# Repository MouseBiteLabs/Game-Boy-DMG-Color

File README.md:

# Game Boy DMG Color

This is my design for an original Game Boy (model name DMG) with native Game Boy Color support, and a handful of improved features! This is an original creation - newly designed PCBs, with only some necessary components harvested from an original Game Boy and Game Boy Color (no hardware emulation – this project uses the original CPU). Here are the project goals:
-	An original Game Boy aesthetic, using the original Game Boy shell and interface (link port, volume wheel, power switch, etc.), but with the capability of playing both Game Boy and Game Boy Color games.
-	A nice, large IPS screen – the GBC Q5 XL IPS Backlight with OSD kit – with brightness and color palette control via the "navigation switch" housed where the contrast wheel used to be. (I will refer to the PCB attached to the Q5 screen as the “Q5 board”)
-	A modernized, efficient switch mode power supply that can run off 4x AA batteries or input from the DC jack, just like the original DMG. Testing shows that playing with NiMH AA batteries can yield more than 18 hours of gameplay at normal settings (AKA, the way I normally play it - maximum brightness and headphones). 
-	Louder, warmer sound through a modern audio amplifier.
-	The option for tactile switches for the face buttons - like the GBA SP.
-	The option for backlit buttons, with multiple color modes and brightness control.
-	No externally viewable case modifications, outside of trimming the DMG power switch cover for Game Boy Color game compatibility.

The code name for this project is DMGC. This console uses four PCBs, just as the original DMG model did - a CPU board (DMGC-CPU), display board (DMGC-IPS), power board (DMGC-PWR), and headphone board (DMGC-HDP). All circuit board assemblies have their own separate folders in this repository which contain detailed descriptions of operation, source files for schematics and board layouts (designed using Eagle), exported Gerber files, and some other relevant files. 

**Do you want to make one?** Then you NEED TO READ this entire page. Seriously. All your questions will be answered.

## Disclaimer

**Before I go any further, please read this VERY important disclaimer, if you are thinking about making this yourself. Don't let this picture happen to you!**

I made this project first and foremost **for my own purposes**. Nearly all of the features I have included are things I **personally** wanted. I have tried my hardest to make the project modular, if others would like to improve or change things easily, and I have also tried very hard to make the design somewhat less prone to potential errors during assembly (such as spacing out power pins on the FFC connectors). But in the end, every decision I made was for what I wanted the final product to be, with my skill level in mind.

Schematics, gerbers, and the BOM are provided in the various folders. If you choose to build this project yourself, be warned - this is a considerably advanced, and expensive build. You must be comfortable with the fact that you may lose or damage expensive components. **You are 100% liable for any damage done to your property or yourself. I am not responsible for any damage or loss of property incurred while attempting this project, or after completion of the project - you alone accept all risk.** While I am confident in this design, I cannot claim full compatibility with every system configuration. And there may be latent issues that have yet to crop up. I will update this repo if I encounter any, and if you see anything I may have missed, or some dubious design choice, feel free to ask questions or comment as such. Corrections are welcome. However, I **will not** obligate myself to providing tech support. You accept all risks and costs associated to this build if you choose to attempt it.

**DO NOT attempt this project if you are uncomfortable or inexperienced with detailed electronics troubleshooting, or are not proficient in soldering! You will AT MINIMUM need to be proficient in drag soldering and hot air reflowing. If you have not gained proficiency in these soldering skills, DO NOT ATTEMPT THIS PROJECT.**

If you attempt the build, start with trying to assemble DMGC-PWR-01. This is the toughest board to assemble, and it requires no donor components.

## Bill of Materials (BOM)

There are a handful of categories for the parts you need for this build. Please review all of them! The total BOM cost will come out to anywhere between $200 and $250 (NOT including the cost of a donor Game Boy Color console!) depending on the options you choose, which OEM parts you re-use, and any potential deals you can get on certain parts. Note that with the exception of a few components from a donor Game Boy Color, *most* of the electronic parts are brand new.

### I. Circuit Boards

First and foremost, the circuit boards. I have created these four boards myself, and you will need all of them:

1) <a href="https://mousebitelabs.etsy.com/listing/1317688422/game-boy-dmgc-cpu-board?utm_source=Copy&utm_medium=ListingManager&utm_campaign=Share&utm_term=so.lmsm&share_time=1694126428997">DMGC-CPU-01</a>: The CPU board, where the brains are held
2) <a href="https://mousebitelabs.etsy.com/listing/1331663235/game-boy-dmgc-ips-board?utm_source=Copy&utm_medium=ListingManager&utm_campaign=Share&utm_term=so.lmsm&share_time=1694126445880">DMGC-IPS-01</a>: The front display board
3) <a href="https://mousebitelabs.etsy.com/listing/1317694018/game-boy-dmgc-pwr-board?utm_source=Copy&utm_medium=ListingManager&utm_campaign=Share&utm_term=so.lmsm&share_time=1694126458438">DMGC-PWR-01</a>: The power supply board
4) <a href="https://mousebitelabs.etsy.com/listing/1331671237/game-boy-dmgc-hdp-board-headphone-board?utm_source=Copy&utm_medium=ListingManager&utm_campaign=Share&utm_term=so.lmsm&share_time=1694126482746">DMGC-HDP-01</a>: The board that holds the headphone jack

I have provided the zipped Gerbers and ordering details in each of the board folders above, <a href="https://www.pcbway.com/project/member/?bmbno=BC9D73E0-EF3D-4F">as well as shared projects on PCBWay.</a> For full disclosure, if you buy the PCBs from PCBWay, I will receive 10% of the total sale towards buying more boards from PCBWay. You can alternatively use these Gerbers at other PCB fabricators if you would like. 

### Purchase from My Website

You can purchase this circuit board at my website, [https://mousebitelabs.store](https://mousebitelabs.store). Click the following image to be directed to the specific item listing:

### Purchase from Etsy

I also offer the board on Etsy, if you would rather purchase through there - click the banner to be redirected.

### Purchase from insideGadgets

And finally, <a href="https://shop.insidegadgets.com/product/game-boy-dmg-color/">insideGadgets sells these boards partially assembled!</a>

### II. Brand New Electronic Parts

The DMGC uses mostly all-new parts. This isn't a direct-transfer style project! The master BOM with every electronic component required for the four circuit boards are provided in this root folder in Excel format. Furthermore, each folder for each board will contain their section of the BOM near the bottom of each README that contain all of the electronic components needed for that specific circuit board. Note that some parts may be out of stock at the links provided, but many can be found at alternate other retailers online, or have a proper substitute. <a href="https://www.mouser.com/ProjectManager/ProjectDetail.aspx?AccessID=6600c1bb14">Here is a saved cart from Mouser that contains all the parts in the BOM Excel, including some duplicates.</a> Double check to see if any parts are missing, and consider ordering multiples of some parts. There also may be some parts you want to remove (like the tactile switches).

**If a part is backordered, or out of stock** - check the Excel file, or the BOMs listed at the bottom of each board's folder in this repo. There may be alternate part options. You can also check for stock at places like Digikey. And you can always use Octopart.com to help find in-stock parts at other websites. I can't maintain the cart for every out-of-stock part, so please do some research :)

### III. Game Boy Electronic Parts

*This project requires at the very least a donor DMG console and a donor GBC console.*

There are a handful of parts that I have not located aftermarket substitutes for, and will therefore necessitate an original Game Boy console to salvage from. Please note that removing these parts is not a trivial task, and **requires advanced soldering and desoldering skills to be successful.**

The following parts are required from an original Game Boy Color console:

  -	U1 – CGB CPU (all revisions *except* REV E, which is *incompatible*)
  - X1 – 8.388 MHz crystal oscillator

The following parts can be salvaged from a Game Boy Color, but aftermarket options exist:

  - U2 – LH52256CVTXIZ (SRAM); alternate: https://mou.sr/3f8G0Mi
  - EM10 – input filter; alternate: https://mou.sr/3FiMvXw

The following parts are required from an original Game Boy (DMG) console:
  
  -	SW1 - Power switch
  -	DC jack
  -	Headphone jack

The following part is required from an original Game Boy (DMG), or a Game Boy Four Player Adapter:

  -	EXT port

The following parts can be salvaged from an original Game Boy (DMG), but aftermarket options exist:

  -	VR1 – Volume dial
  -	P1 – Cartridge connector

### IV. External Build Parts

The following is the high-level BOM - basically, the Game Boy part. Note that parts that deviate from the ones listed here (like different shell designs) might necessitate different fitment modifications, or end up being incompatible. Note that this list is not a comprehensive list of all the places you can get these parts. I encourage you to search around if you can't find what you want here.

-	**Shell:** I generally recommend the Funnyplaying "IPS Ready" ones if you don't want to trim anything, but the color and style options are limited. If you don't use these, then you're on your own for how to prepare it - generally, you can follow guides for preparing a Pocket for an IPS screen kit.
    - RGRS:	<a href="https://retrogamerepairshop.com/collections/game-boy-dmg-shells/products/game-boy-dmg-original-new-shells-factory-a?variant=32530346967114">Game Boy DMG Shell – Factory A</a> [Note: this one requires trimming!]
    - Funnyplaying: <a href="https://funnyplaying.com/products/dmg-ips-coustom-housing">DMG IPS Q5 Custom Housing</a>
- **Screen Kit:** This is the important one. You need this specific type of kit - the Q5 IPS with OSD. It goes by many names, the maker is Hispeedido (*not* FunnyPlaying). Kits that have the screen laminated to a GBC lens are *not* compatible, but kits that include a lit-up logo on the bottom part of the screen are fine to use. Make sure you DO NOT get any Game Boy DMG versions - they are not compatible! Also, be sure to test this screen kit before installing it, preferrably with an original Game Boy Color. Sometimes they arrive damaged, and once you've installed, it may not be possible to get a refund.
  - RGRS: <a href="https://retrogamerepairshop.com/products/game-boy-color-q5-ips-backlight-with-osd?variant=37646279213228">GBC Q5 XL IPS Backlight with OSD</a> OR <a href="https://retrogamerepairshop.com/collections/gbc-displays/products/game-boy-color-q5-osd-ips-kit-with-color-changing-logo?variant=41819042185388">Game Boy Color Q5 OSD IPS Kit with Color Changing Logo 
  - AliExpress: <a href="https://www.aliexpress.us/item/3256801650459088.html?spm=a2g0o.productlist.main.1.758e53f17WUFK2&algo_pvid=24ef67e3-d608-4269-a663-05eafed1bd17&algo_exp_id=24ef67e3-d608-4269-a663-05eafed1bd17-0&pdp_npi=3%40dis%21USD%2145.9%2145.9%21%21%21%21%21%4021224e9b16816641208271256d074d%2112000017802039303%21sea%21US%210&curPageLogUid=dCymHIE0cr4X">GBC Q5 IPS LCD Kit</a>
  - HHL: <a href="https://handheldlegend.com/products/game-boy-color-ips-lcd-q5-hispeedido">Game Boy Color IPS LCD Q5 - Hispeedido</a>  
- **Screen Centering Bracket:** You can find the design file for this bracket in the DMGC-IPS-01 folder. It's a custom designed bracket I made that *is required* for holding the screen in place. You will need access to a 3D printer for this part, or you can order it online from 3D printing services by uploading the file.
  - <a href="https://github.com/MouseBiteLabs/Game-Boy-DMG-Color/blob/main/DMGC-IPS-01/dmgc_q5_bracket.stl">DMGC Q5 Bracket 3D Model .stl File</a>
-	**Lens:** You must get the "IPS" style of lens, as the viewing area is larger.
    -	RGRS: <a href="https://retrogamerepairshop.com/collections/dmg-lenses/products/funnyplaying-dmg-q5-ips-lens?variant=39626455187628">FunnyPlaying DMG Q5 IPS Lens</a>
    - FunnyPlaying: <a href="https://funnyplaying.com/products/dmg-retro-pixel-ips-glass-lens">DMG RetroPixel IPS Glass Lens</a>
- **Buttons:** Funnyplaying models are generally OEM-like (IMO), but you can also use OEM ones. For the above build, I used Kitsch-Bent silicone buttons. Bonus: NES controller buttons fit inside the DMG.
  -	Kitsch-Bent: <a href="https://store.kitsch-bent.com/products/silicone-buttons?variant=40627510771907">Clear Silicone DMG Buttons</a>
  - RGRS: <a href="https://retrogamerepairshop.com/collections/dmg-buttons">DMG Buttons</a>
  - LabFifteen: <a href="https://labfifteenco.com/en-us/collections/game-boy-dmg-buttons">Game Boy DMG Buttons</a>
  - FunnyPlaying: <a href="https://funnyplaying.com/products/gb-dmg-custom-buttons">DMG Custom Buttons</a>  
- **Membranes:** Important, but very forgettable! You will need them even if you install tactile switches. You will, however, *not* need them if you use the Kitsch-Bent buttons.
  - RGRS: <a href="https://retrogamerepairshop.com/collections/dmg-buttons/products/funnyplaying-game-boy-dmg-silicone-button-contact-pad-membranes">FunnyPlaying Game Boy DMG Silicone Button Contact Pad Membranes
  - FunnyPlaying: <a href="https://funnyplaying.com/products/replacement-silicone-pads-for-gb-dmg">DMG Replacement Silicone Pads</a>  
- **Speaker:** There are tons of options for this as well, including using the OEM one.
  - RGRS: <a href="https://retrogamerepairshop.com/collections/dmg-audio/products/funnyplaying-clear-game-boy-dmg-original-speaker?variant=37728957726892">FunnyPlaying Clear Game Boy DMG Original Speaker</a>
  - FunnyPlaying: <a href="https://funnyplaying.com/products/clear-dmg-speaker">Clear DMG Speaker</a>
- **Battery Tabs:** This one is another part I commonly forget about. You can use a salvaged set of tabs, or order new ones.
  - RGRS: <a href="https://retrogamerepairshop.com/collections/dmg-power/products/game-boy-dmg-original-high-quality-replacement-battery-contact-terminals?variant=37893135794348">Game Boy DMG Original High Quality Replacement Battery Contact Terminals
- **Stickers:** Completely optional, but they can really bring a build together. Especially if you have custom DMG Color stickers!
  - Nextstopplease: <a href="https://nextstopplease.square.site/product/dmgc-label/230?cp=true&sa=true&sbp=false&q=false">DMGC Labels</a>

<b>Buying from RGRS? Consider helping out some cool people with these referral links:</b>
- <a href="https://retrogamerepairshop.com/?ref=ltyD2rUX">CodyWick</a>
- <a href="https://retrogamerepairshop.com/?ref=HSj4v5OO">JackV</a>

<b>Or use one of these discount codes at checkout:</b>
- Nataliethenerd
- B23N
- Tito

Note that the IPS kit I have listed is the *easiest* IPS kit to use that is compatible with this build. It includes an image centering feature, so you don't need to fiddle with centering it manually in the shell. Other kits likely would not center nicely in the DMG shell! <a href="https://retrogamerepairshop.com/collections/gbc-displays/products/game-boy-color-2-6-ips-high-brightness-drop-in-backlight-lcd-kit?variant=41398632251564">This kit works electrically, but requires you to center the image yourself.</a> If you end up making some sort of 3D-printed bracket to support this screen, feel free to share it here.

## Assembly

You can check out Tito's video on the DMGC to get an idea of how the assembly process generally goes.

Here are some pictures of the assembly process *after* testing the functionality of all the boards separately. Detailed images of the circuit boards alone are shown in their respective folders. These pictures are of a previous revision, v1.2, but the process remains the same. You may notice some minor cosmetic differences in these pictures from the current revision boards.

**I highly recommend reading the information in the Troubleshooting and Testing folder above. In it, I detail the testing procedure that I follow before fully assembling a DMGC. It is far easier to do this than to have to disassemble things when something doesn't work.**

First, I started with the back half of the DMG shell. The PWR board needs five ~2.25" wires that wrap around the screw post on the side of the shell. In addition to the PWR board connections, the HDP board needs four ~2.6" wires. Also, the flat flex cable (FFC) should be inserted into the CPU board first, because the connector will be inaccessible after screwing the CPU board in the shell. After I soldered all the wires between the three boards and secured the FFC, I placed the assembly in the shell, and secured it with the proper screws. I put a game in the cartridge slot to keep the CPU board in place easier while assembling.

Before placing the power switch cover in, I cut a notch in it so that it wouldn't prevent Game Boy Color games from being played in the system. In the left picture below I’m using Game Boy games, and in the right picture I'm using Game Boy Color. And you can see that the power switch is blocked from turning on by the GBC cartridge for the original model.

After the back half was done, I prepared the Q5 board solder pads. I cut six 30 gauge wire segments and soldered them on the brightness, palette, battery, and OSD input pads. These will be soldered to the rear of the IPS board after installed. You don't need to include a wire to the GND pad.

For the top half of the shell, as per instructions on a similar DMG IPS kit that uses the Q5 screen, I very carefully cut ~1 mm of plastic around the border of the viewing port, and trimmed any extra plastic to make the surface underneath the lens smooth (there are "IPS ready" shells that should not require this cut). I used a black paint marker to color in the edges of the newly cut plastic, so they would not be visible at an angle. And I trimmed two posts off of the shell so the screen would fit flush against it. 

Then I installed the front lens, and placed the screen, backed with the 3D printed bracket, into the front half of the shell. I made sure to clean up any stray fingerprints or dust while assembling this part. Once the bracket was placed and flush with the shell, I put the buttons in and placed the IPS board over top, slid the Q5 screen FFC into the connector on the PCB (making sure it fit without any added stress on any connections), and secured it all in place. Then I *very carefully* soldered the wires from the Q5 board onto the appropriate pads on the IPS board - making sure not to melt any plastic on the shell.

**Note: Be extremely careful with the screen. It is fragile. If you break it, you can sometimes buy one separately.

If you installed the 7-pin headers for programming the ATTINY easier, you might want to tape off the headers with kapton tape. If everything is installed correctly, these shouldn't interfere with anything on the CPU board after the halves are screwed together (C47 is the closest component), but you may want to consider it anyway.

After that, it was just a matter of connecting the FFC from the CPU to the IPS board, tucking it under the boards ensuring no kinks or sharp bends, and screwing it together. Once assembled, I opened the OSD menu for the IPS kit (Select + A + B) and changed the vertical and horizontal offsets (my values were 78 and 29, respectively) to center the image on the screen. The image centering function is one of the biggest reasons I chose this IPS kit.

I suggest running the color tests in the <a href="https://github.com/pinobatch/240p-test-mini/releases/">240p test suite ROM</a>, if you have a flash cart to run it on. It will tell you if you have any poor connections on the FFC lines - the screen might work, but you might be missing a connection on one of the 15 RGB pins! If your colors look off, reflow the connections on the top row of pins on the CPU and/or the FFC connectors (the issue may be on the CPU board, *or* the IPS board). This picture (provided by <a href="https://retrogamerepairshop.com/?ref=HSj4v5OO">JackV</a>) shows a before and after pic for reflowing a few mis-soldered color pins.

Next to an original DMG… one can really see the improvements!

## Auxilliary Controls
### Q5 XL IPS Backlight with OSD
-	Select + A + B: Open the OSD menu
-	Select + A: Enter
-	Select + B: Exit
-	A: Increase
-	B: Decrease

### Navigation Switch
-	Rock up: Advance screen brightness setting
-	Rock up/Hold: Toggle on-screen battery indicator
-	Rock down: Advance screen color pallete setting
-	Rock down/Hold: Toggle on-screen pixel grid
-	Push in: Toggle button LED color setting
-	Push in/Hold + D-pad Left: Decrease button LED brightness
-	Push in/Hold + D-Pad Right: Increase button LED brightness
-	Push in/Hold when turning on power switch: Disable LEDs until another power cycle

## Power Draw Measurements
For these estimates, battery life is calculated using four eneloop pro NiMH AA batteries (total of ~11800 mWh). Keep in mind that these are very rough estimates. I tried to be conservative in the power draw measurements, so hopefully these numbers represent a *mostly* worst case. Actual playtime *will* vary due to a variety of factors - changes in efficiency and performance as the battery voltage changes, differences in game audio, etc.

I measured the power draws using a MiniWare MDP-XP Mini Digital Power Supply, and estimated the average power draw shown on the display (I tried to bias towards a higher value). Input voltage was set to 4.4 V, just above the point where the power LED dims. I tested with the Legend of Zelda: Link's Awakening, letting the game sit on the title screen after the intro cinematic, where sound is relatively loud and the screen is mostly white. The audio gain on the test console is set to ~0.38 (see CPU board for more detail on this gain value - a higher gain can greatly impact power draw at high volumes out of the speaker).

| Test Criteria | Power Draw | Estimated Battery Life |
| ------------- | ------------- | ------------- |
| IPS max brightness, NeoPixel LEDs max brightness (white), speaker volume 100%, Everdrive X5	| 1150 mW	| 10.3 hr |
| IPS max brightness, NeoPixel LEDs off, speaker volume 100%, Everdrive X5 | 900 mW	| 13.1 hr |
| IPS max brightness, NeoPixel LEDs off, speaker volume 100%, original cartridge | 750 mW | 15.7 hr |
| IPS max brightness, NeoPixel LEDs off, headphones, Everdrive X5	| 725 mW	| 16.3 hr |
| IPS max brightness, NeoPixel LEDs off, headphones, original cartridge | 650 mW	| 18.2 hr |
| IPS min brightness, NeoPixel LEDs off, headphones, original cartridge	| 475 mW	| 24.8 hr |

*Note: If powering through the DC jack instead of batteries, an OEM adapter may not be able to supply enough power to the DMGC at maximum settings. Furthermore, <a href = "https://retrogamerepairshop.com/products/dmg-game-boy-original-dmg-usb-power-cord-adapter?variant=39454726455468">cables like these</a> will require at least ~200 mA output from the USB port for reliable operation at all settings. (USB 1.0 and 2.0 are likely not sufficient for higher loads, such as with the button LEDs on)*

## Audio Recordings and Spectrum
I mentioned the sound of the DMGC is "warmer" than an original GBC - it's bassier with less buzzing background noise (owing mostly to the modernized power supply). I connected the headphone jack to my computer's microphone input, and used Audacity to obtain line out recordings. Then I graphed the spectrum using Audacity's "plot spectrum" analysis tool. You can see the larger gain at the lower frequencies in the spectrum plot of the DMGC. I also took some recordings of the pro-sound output as well - it's even cleaner than from the amplifier. I'm not an audiophile, but I'm pretty sure the DMGC all-around sounds nicer, at least through headphones. Listen for yourself! (GitHub only allows for video files to be embedded, MP3 files are provided above)

### Original GBC Audio

https://user-images.githubusercontent.com/97127539/180215249-4b21aca1-a9fd-430a-a870-95bf4837e4da.mp4

### DMGC Audio

https://user-images.githubusercontent.com/97127539/180215280-5e533449-5116-4848-a94b-92f8979db334.mp4

### DMGC Audio (Pro-sound)

https://user-images.githubusercontent.com/97127539/197674317-792a8da5-ebd5-4ef6-9e8d-8eab0cbf9284.mp4

### Original GBC Audio Spectrum

### DMGC Audio Spectrum

### DMGC Audio (Pro-sound) Spectrum

## Possible Additions/Changes
Want to improve this project? Maybe try one of these things (because I probably won’t):
- This console uses 4x AAs instead of a single rechargeable battery in order to maintain the feel and weight of the original DMG model, but an obvious change to the build is to utilize a LiPo battery with proper battery management. The DC jack could be repurposed to charge the battery instead. With the advent of affordable rechargeable AAs, the appeal of the AC adapter is diminished, so this would be a good repurposing. However, the maximum output current of most DMG AC adapters is rated for ~200mA at ~6V, so charging would be considerably slower than, say, fast USB-C charging.
- Restoring the IR functionality of the GBC could also be done, as there is ample space for it on the circuit board and shell - I just do not trust myself with forming plastic to look nice, and it wasn't at all an important part of the build for me.
- Finding aftermarket equivalents for all the different required DMG parts would be ideal, instead of using a (hopefully broken) DMG for a donor console. For my personal build, I used original DMG components because I had a damaged console lying around, but you can easily find DMG-style volume wheels and cartridge connectors online. The tricky parts are as follows:
  - A GBC EXT port can be used in place of the DMG one (but would look kind of weird in the DMG EXT hole in the shell).
  - There are a few power switches I've ordered to try out in place of the DMG one, but I haven't gotten around to testing them yet. There's no one fully drop-in replacement that I've found, though, so it would require circuit modifications.
  - I haven't been able to locate a headphone jack exactly the same as the DMG one, but the circuit could be adapted to accept a different style.
  - The DC jack could be tricky. I haven't looked very hard for any kind of replacement for this.
- Any other of the various popular GBC mods could be incorporated if desired - bluetooth, overclocking, etc. With the ATTINY on the IPS board, one could incorporate button combinations to interface with these mods without the need of any additional buttons or (*shudder*) touch controls.
- I thought about adding LEDs to the *back* of the front PCB, so that light would emit out the edges of the console with a translucent or transparent shell, but I never got around to trying it out.

## Potential Issues/Annoyances
-	When the button LEDs are on max brightness, using the NeoPixel LEDs specifically (especially on the white color setting), a ~1 kHz whine can be heard through the speakers or headphones. I attempted to remove this whine with different methods – adding filtering to the supplies, using separate supplies for the audio/LEDs, etc. –  this lowered the noise amplitude, but I wasn’t able to remove it completely. And obviously adding a filter on the audio output is a no-go since 1 kHz is smack dab in the middle of the audible range. Changing to different color settings can reduce the volume of the whine, red in particular seems to be quite low, and setting the LEDs at lower brightness levels (or just completely off) removes it. So just don’t play with the LEDs on really bright if it bugs you! I kept the color sweep during power-on enabled on every color setting - if you want to disable the LEDs for the entire play session, hold the navigation dial in when you turn it on (but at that point... why did you bother adding the LEDs in the first place?)
-	The original DMG A/C adapter that plugs into the DC jack cannot support play with maximum settings (backlit buttons, maximum brightness, maximum speaker volume, flash cart). If you start up the Game Boy with less than maximum settings, then during gameplay increase the load on the power supply such as by increasing the screen brightness or maxing out the volume on the speakers, the console may shut off. If you're powering the console through the DC jack, I suggest using a USB adapter cable into a USB 3.0 port (or some style of USB wall charger)

## Frequently Asked Questions

I'll update this section as more people begin to build these.

**Q: How do I lower the brightness of the power LED? I can't see anymore.**

A: You can pick a different LED model with lower brightness, or you can simply increase the resistance of R1 on the IPS board. Higher resistance = lower brightness. I would try 10 kΩ first if 5.6 kΩ is too bright. (If you want to dim the low power level LED brightness, increase R2 resistance as well!)

**Q: My EM10 has an extra leg in-between two of the other ones. Can I use this part?**

A: Yes, just bend up the extra pin so that it doesn't contact any of the nearby pads. It is an unused anchor pin.

**Q: Why does the audio sound like [not normal]? (Usually asked while testing during the middle of a build)**

A: The audio will sound terrible if you do not have your IPS kit connected. You can use the CPU board's FFC connnector for the IPS kit if you would like to test it without the IPS board in the middle. Furthermore, the speaker will be muted if you do not install the headphone board.

**Q: Sometimes the power switch is finnicky and the system won't power on consistently. Sometimes the IPS screen will turn on, but only the backlight, not the actual image. What gives?**

A: Clean your power switch (without batteries inserted or power applied) by dripping isopropyl alcohol inside and flipping it off and on a few times. This will hopefully clear up debris or oxidation. Opening up a DMG power switch isn't the funnest thing to do. I have found that if the IPS kits receive intermittent power while turning on, it will lock out their image processing until you power cycle. It's not damaging, just annoying.

**Q: When I have the front and back halves of the DMGC separate, everything powers on correctly. But when I screw the two halves together, it doesn't turn on. Why?**

A: Check to make sure the wires connecting the CPU and PWR boards do not have long stubs of wire sticking up out of the CPU board. The IPS board's navigation dial has metal housing that can short these wire stubs together if they are too long. Trim them short so they don't touch the metal shielding.

**Q: Sometimes when I'm using batteries and turn the power switch on, nothing happens.**

-AND/OR-

**Q: Sometimes when I play my DMGC, and I set it on the table too hard, the game resets. Why?**

A: Usually this is because you're using NiMH AA batteries, like eneloop pros. These batteries have *slightly* shallower positive tabs than regular alkaline AA batteries. This makes contact from the batteries to the tabs not as robust as regular AA batteries. Unfortunately this is a problem on *ALL* DMG consoles, not specifically the DMGC. This could be due to a poor connection on any one of the four batteries inside the bay. You can swap out battery contacts that stick out a bit farther that make better contact with the batteries, or you can try reseating or literally spinning the batteries in the battery bay to make better contact. (Or, you could always use regular AA batteries or an A/C adapter!)

**Q: Can I use this with a DMG CPU?**

A: No, this is only for use with Game Boy Color CPUs. There are some other projects around that recreate the DMG, <a href="https://github.com/kamicane/DMG-01-B">like this one</a>.

**Q: I really like this project, but I just wish it was in a smaller, more cramped shell, with way worse battery life. Can you help?**

A: <a href="https://imgur.com/a/JgXPnYc">I'm working on it.</a>

## Acknowledgements
-	The board outlines and many of the footprints for the DMG components from <a href="https://gbdev.gg8.se/files/schematics/">this DMG recreation project</a> were used for reference on the original revision of the project, so very special thanks to Rolf, bit9, and nitro2k01!
-	Thank you to gekkio for their <a href="https://gbhwdb.gekkio.fi/">Game Boy repository</a> and <a href="https://github.com/Gekkio/gb-schematics">github</a>: I referenced many of the DMG and GBC resources during this build, even just for looking at pictures of different PCBs.
-	Immense thanks to the users of the r/Gameboy and gbdev discord servers for technical resources, troubleshooting/feedback, and suggestions. Could not have done this without your support. Shout out to kevtris for design feedback and lidnariq for troubleshooting support!
- Thank you to Tito, aka Macho Nacho, for <a href="https://www.youtube.com/watch?v=4U8Tqu7uxLo&ab_channel=MachoNachoProductions">his amazing video covering the project.</a>
-	Of course, huge thank you to everyone who has <a href="https://ko-fi.com/bucketmouse">donated and supported me</a>, and to those who have built their own DMGC! I love seeing pictures of builds, so feel free to share them with me on Twitter, <a href="https://discord.gg/Y5aDvCcpbX">discord</a>, or via email!

## License
<br />This work is licensed under a <a rel="license" href="http://creativecommons.org/licenses/by-sa/4.0/">Creative Commons Attribution-ShareAlike 4.0 International License</a>. You are able to copy and redistribute the material in any medium or format, as well as remix, transform, or build upon the material for any purpose (even commercial) - but you **must** give appropriate credit, provide a link to the license, and indicate if any changes were made.

This project is the culmination of nearly a full year of research, development, and testing. I have made this project completely open-source, and have put hundreds, if not *thousands* of hours of work into it, so that many people can enjoy it. **Please** give me appropriate credit where credit is due.

©MouseBiteLabs 2022

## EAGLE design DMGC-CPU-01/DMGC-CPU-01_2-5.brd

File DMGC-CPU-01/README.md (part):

# DMGC-CPU-01

*The image above of the assembled board is of v2.0, not the current revision of v2.4. The differences in appearance are minor, see below.*

The CPU board houses the majority of the electronics in the DMGC. Parts harvested from the original GBC include the CPU, SRAM, and crystal oscillator. EM10 may be transferred as well, but a good enough replacement is included in the BOM if you need a new part. The power supply modifications, the new audio circuit, and a handful of omissions like the IR communication and some of the now-unnecessary LCD pins differentiate this build from the original GBC. But many connections and component values are pulled from the official GBC schematic (linked below).

For a technical explanation of the CPU board, please view the README in the Technical folder.

## Board Characteristics
The zipped folder contains all the gerber files for this board. 

-	Layers: 2
-	Thickness: 1.2 mm
-	Surface Finish: ENIG or HASL
-   **NOTE: For v2.4, when ordering PCBs, add this note to the order: "The file milling.gbr contains outlines for plated slots. Please add plated slots on the PCB according to this layer." V2.5 does not require this note.**

*HASL will work, but will potentially be more difficult for soldering fine-pitch parts like the CPU and FFC connector.*

<a href="https://www.etsy.com/listing/1317688422/game-boy-dmgc-cpu-board">**I sell this board on Etsy, so you don't have to buy multiples from board fabricators.**</a>

You can alternatively use the zipped folder at any board fabricator you like. You may also buy the board from PCBWay using this link (disclosure: I receive 10% of the  sale value to go towards future PCB orders):

## Customization Options

This section will explain all of the different customization options available on this board while assembling.

### Adjusting Volume Range

You can adjust the maximum volume coming out of the speakers and headphones by modifying R30 and R32 values. Increase R30 and R32 to decrease the maximum volume; decrease R30 and R32 to increase the maximum volume. Choose the same values for both of these resistors, otherwise you'll have lopsided audio channels. After some trial and error, here's my approximations of some different values of resistors:
- Choosing 100 kΩ for a gain of ~0.18 will yield about the same volume as a stock GBC. 
- Using 47 kΩ seemed to hit a sweet spot for my tastes for a gain of ~0.38 - not too loud, not too quiet.
- The lowest value I tried out was 33 kΩ, but this was *considerably* loud. It also began to have an actual impact in the battery voltage. I suspect values lower than about 20 kΩ will greatly reduce battery life.

### Pro-Sound Output

Added in version 2.0, opposite of the regular headphone outputs, are a set of audio outputs denoted as "pre-pot audio." The left and right channels connect directly to the VR1-S01 and VR1-S02 nodes, which allows you to grab the audio unfiltered, unamplified, right from the GBC CPU (through a protection resistor/capacitor combo). This is colloquailly known as the "pro-sound" mod, and is typically used in conjunction with a *second* audio jack. Audiophiles like to use this raw output with their audio equipment (note that using the pro-sound output as input to an external amplifier does not disable the speaker or headphones - the potentiometer still controls volume for those audio outputs). You could use this jack for headphones if you want (and it will disable the speaker), but it will always be one volume - about as loud as the original GBC at max volume. The audio coming out of these pins does sound incredibly clean - check out the recordings in the root folder. These outputs should make the system compatible with any pro-sound headphone boards, <a href="https://www.retromodding.com/products/gameboy-pcb-mount-pro-sound-v3">like this one.</a>

### Adding Reset Button Functionality

Version 2.0 also introduces a test pad labelled "RST" that connects directly to the /RESET pin. If this pin is pulled to GND, when it's released it the system will reset back to the boot screen. If you wire this pad to a button that connects the pad to GND when pressed, you basically have added a reset button to your DMGC. 

There are also pads near the FFC connector that are added labelled "PUSH" and "ROCK DOWN". These connect to the rocker switch on the DMGC-IPS-01 board (version 2.0 and later). The PUSH pad becomes connected to GND when the rocker switch is pushed in and floats when not pressed (as long as you remove R10 on the DMGC-IPS-01 board). The ROCK_DOWN pad connects to GND when the rocker switch is rocked down, and floats when not pressed (as long as you remove C5 on the DMGC-IPS-01 board).

In a normal configuration, pushing in on the rocker switch will control the button LEDs, and rocking down will swap the Q5 color settings, but if you don't want to use one of these features, then adding a wire from the PUSH or ROCK DOWN pad to RST pad will turn the rocker switch into a reset button for the system for that specific action and replace its normal function.

**CAUTION: Remember to remove R10 or C5 on the IPS board if you plan to use this feature!!!**

## Bill of Materials

Here, I have provided links to components I used personally (or suitable replacements). This BOM is also included in Excel format in the root folder.

| Reference Designators                       | Qty | Value/Part Number | Package     | Description        | Comment                                                                 | Source                                                                                                                                                                                                                                                                                                                           |
| ------------------------------------------- | --- | ----------------- | ----------- | ------------------ | ----------------------------------------------------------------------- | -------------------------------------------------------------------------------------------------------------------------------------------------------------------------------------------------------------------------------------------------------------------------------------------------------------------------------- |
| +,-                                         | 2   |                   |             | Battery terminals  | Can be salvaged from DMG instead                                        | [https://retrogamerepairshop.com/collections/dmg-power/products/game-boy-dmg-original-high-quality-replacement-battery-contact-terminals?variant=37893135794348](https://retrogamerepairshop.com/collections/dmg-power/products/game-boy-dmg-original-high-quality-replacement-battery-contact-terminals?variant=37893135794348) |
| C1                                          | 1   | 18pF              | 0603        | Capacitor (MLCC)   | Should be X5R (or better); at least 1% tolerance; at least 16V          | [https://www.mouser.com/ProductDetail/YAGEO/CC0603FRNPO9BN180?qs=vTakOoo5QyL0KzYUzHPSUw%3D%3D](https://www.mouser.com/ProductDetail/YAGEO/CC0603FRNPO9BN180?qs=vTakOoo5QyL0KzYUzHPSUw%3D%3D)                                                                                                                                     |
| C2                                          | 1   | 27pF              | 0603        | Capacitor (MLCC)   | Should be X5R (or better); at least 1% tolerance; at least 16V          | [https://www.mouser.com/ProductDetail/603-C0603FRNPO9BN270](https://www.mouser.com/ProductDetail/603-C0603FRNPO9BN270)                                                                                                                                                                                                           |
| C4                                          | 1   | 22pF              | 0603        | Capacitor (MLCC)   |                                                                         | [https://www.mouser.com/ProductDetail/YAGEO/CC0603JRNPO9BN220?qs=vTakOoo5QyIVMYOUTI%2F4zA%3D%3D](https://www.mouser.com/ProductDetail/YAGEO/CC0603JRNPO9BN220?qs=vTakOoo5QyIVMYOUTI%2F4zA%3D%3D)                                                                                                                                 |
| C5, C6, C7                                  | 3   | 100pF             | 0603        | Capacitor (MLCC)   |                                                                         | [https://www.mouser.com/ProductDetail/YAGEO/CC0603JPNPO9BN101?qs=7s%252B3O6pAiyAo%2FUxNqKltRA%3D%3D](https://www.mouser.com/ProductDetail/YAGEO/CC0603JPNPO9BN101?qs=7s%252B3O6pAiyAo%2FUxNqKltRA%3D%3D)                                                                                                                         |
| C9, C10, C29, C33, C41, C45                 | 6   | 0.01uF            | 0603        | Capacitor (MLCC)   | Should be X5R (or better), at least 16V                                 | [https://www.mouser.com/ProductDetail/KEMET/C0603C103J5RACTU?qs=BimOss5pjlFJEfKhlb7g1g%3D%3D](https://www.mouser.com/ProductDetail/KEMET/C0603C103J5RACTU?qs=BimOss5pjlFJEfKhlb7g1g%3D%3D)                                                                                                                                       |
| C16, C17, C18, C19, C39, C40, C48, C49, C51 | 9   | 1uF               | 0603        | Capacitor (MLCC)   | Should be X5R (or better), at least 16V                                 | [https://www.mouser.com/ProductDetail/KEMET/C0603C105K4RACTU?qs=STjISULpmtZNMAZGR4X39Q%3D%3D](https://www.mouser.com/ProductDetail/KEMET/C0603C105K4RACTU?qs=STjISULpmtZNMAZGR4X39Q%3D%3D)                                                                                                                                       |
| C24, C28, C43, C52, C53                     | 5   | 0.1uF             | 0603        | Capacitor (MLCC)   | Should be X5R (or better), at least 16V                                 | [https://www.mouser.com/ProductDetail/?qs=l5k%252BbMnNDknCtKnMv1oEgA%3D%3D](https://www.mouser.com/ProductDetail/?qs=l5k%252BbMnNDknCtKnMv1oEgA%3D%3D)                                                                                                                                                                           |
| C47                                         | 1   | 150pF             | 0603        | Capacitor (MLCC)   |                                                                         | [https://www.mouser.com/ProductDetail/KEMET/C0603C151J5GACTU?qs=V6nSPVTm7vxbAvL0weNH%252BQ%3D%3D](https://www.mouser.com/ProductDetail/KEMET/C0603C151J5GACTU?qs=V6nSPVTm7vxbAvL0weNH%252BQ%3D%3D)                                                                                                                               |
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
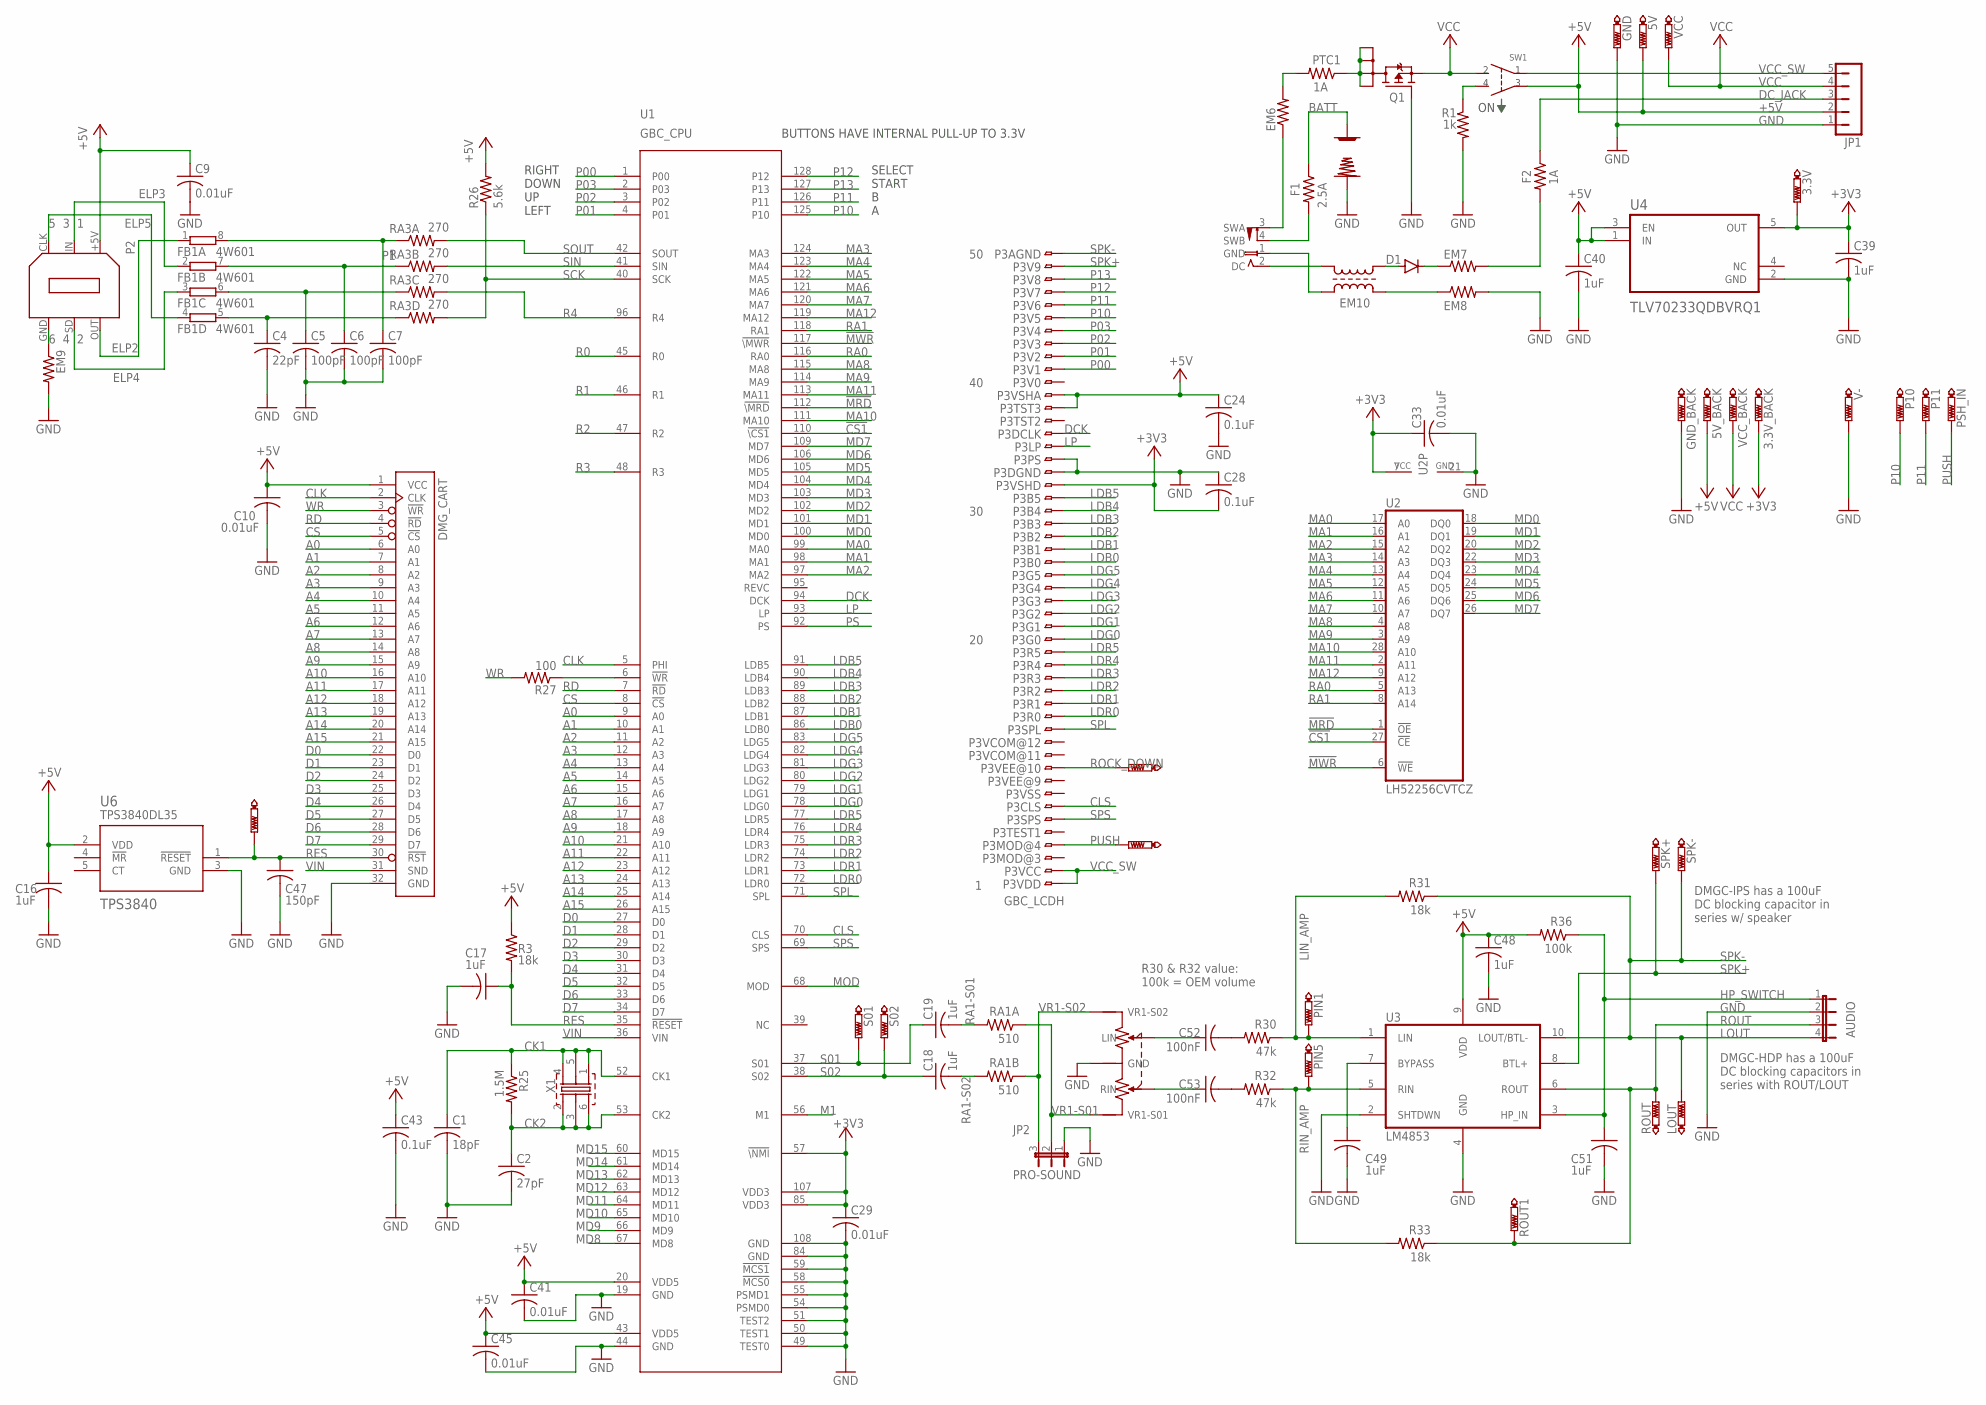
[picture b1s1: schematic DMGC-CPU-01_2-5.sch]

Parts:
3.3V, 3.3V_BACK, 5V, 5V_BACK: PTR1B1,27; B1,27
+: DMG_BAT_POS
-: DMG_BAT_NEG
AUDIO: JP4E; JP4
C1: 18pF; C0603
C2: 27pF; C0603
C4: 22pF; C0603
C5, C6, C7: 100pF; C0603
C9, C10, C29, C33, C41, C45: 0.01uF; C0603
C16, C17, C18, C19, C39, C40, C48, C49, C51: 1uF; C0603
C24, C28, C43: 0.1uF; C0603
C47: 150pF; C0603
C52, C53: 100nF; C0603
D1: CGRM4001-G; SOD-123_MINI-SMA
DC: DMG_DCJACK
EM6, EM7, EM8: BLM21P221SG; R0805
EM9: BLM21P221SG; R0603
EM10: ACM4532-801-2PA; ACM4532
F1: 2.5A; R1206
F2: 1A; R1206
FB1: 4W601; EXB38V
GND: PTR1B1,27; B1,27
GND_BACK: PTR1B1,27; B1,27
JP1: JP5
JP2: JP2E; JP2
LOUT: PTR1B1,27; B1,27
P1: DMG_CART
P2: LINKPORTDMG-LINK-SHORT; DMG_EXT
P3: GBC_LCDH; 62684-502100AHLF
P10, P11: PTR1B1,27; B1,27
PIN1, PIN5: PTR1B1,27; B1,27
PSH_IN: PTR1B1,27; B1,27
PTC1: 1A; R1206
PUSH: PTR1B1,27; B1,27
Q1: SI1401EDH; SOT363_INFINEON
R1: 1k; R0603
R3, R31, R33: 18k; R0603
R25: 1.5M; R0603
R26: 5.6k; R0603
R27: 100; R0603
R30, R32: 47k; R0603
R36: 100k; R0603
RA1A, RA1B: 510; R0603
RA3A, RA3B, RA3C, RA3D: 270; R0603
ROCKDOWN: PTR1B1,27; B1,27
ROUT, ROUT1: PTR1B1,27; B1,27
RST: PTR1B1,27; B1,27
S01, S02: PTR1B1,27; B1,27
SPK+: PTR1B1,27; B1,27
SPK-: PTR1B1,27; B1,27
SW1: DMG_SW
U1: GBC_CPU; QFP-128
U2: LH52256CVTCZ; TSOP1-28
U3: LM4853; VSSOP10
U4: TLV70233QDBVRQ1; SOT95P280X145-5N
U6: TPS3840; SOT-23-5
V-: PTR1B1,27; B1,27
VCC: PTR1B1,27; B1,27
VCC_BACK: PTR1B1,27; B1,27
VR1: DMG_VOL
X1: 8.388608MHZ12SMX-B-4-PAD; 7.5X5-4-PAD

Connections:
!CS1: U1.110 (!\CS1), U2.27 (!CE)
!MRD: U1.112 (!\MRD), U2.1 (!OE)
!MWR: U1.117 (!\MWR), U2.6 (!WE)
+3V3: 3.3V.TP, 3.3V_BACK.TP, C28.2, C29.1, C33.1, C39.1, P3.32, U1.57 (!\NMI), U1.85 (VDD3), U1.107 (VDD3), U2.7 (VCC), U4.5 (OUT)
+5V: 5V.TP, 5V_BACK.TP, C9.1, C10.1, C16.1, C24.1, C40.1, C41.1, C43.1, C45.1, C48.1, JP1.2, P1.1 (VCC), P2.+5V, P3.38, P3.39, R3.1, R26.2, R36.2, SW1.P$3 (3), U1.20 (VDD5), U1.43 (VDD5), U3.9 (VDD), U4.1 (IN), U4.3 (EN), U6.2 (VDD)
A0: P1.6 (A0), U1.9 (A0)
A1: P1.7 (A1), U1.10 (A1)
A2: P1.8 (A2), U1.11 (A2)
A3: P1.9 (A3), U1.12 (A3)
A4: P1.10 (A4), U1.13 (A4)
A5: P1.11 (A5), U1.14 (A5)
A6: P1.12 (A6), U1.15 (A6)
A7: P1.13 (A7), U1.16 (A7)
A8: P1.14 (A8), U1.17 (A8)
A9: P1.15 (A9), U1.18 (A9)
A10: P1.16 (A10), U1.21 (A10)
A11: P1.17 (A11), U1.22 (A11)
A12: P1.18 (A12), U1.23 (A12)
A13: P1.19 (A13), U1.24 (A13)
A14: P1.20 (A14), U1.25 (A14)
A15: P1.21 (A15), U1.26 (A15)
BATT: +.P$1, F1.1
BATT_DC: DC.3 (SWA), EM6.1
CK1: C1.1, R25.1, U1.52 (CK1), X1.1, X1.4, X1.5
CK2: C2.1, R25.2, U1.53 (CK2), X1.2, X1.3, X1.6
CLK: P1.2 (CLK), U1.5 (PHI)
CLS: P3.7, U1.70 (CLS)
CS: P1.5 (!CS), U1.8 (!CS)
D0: P1.22 (D0), U1.27 (D0)
D1: P1.23 (D1), U1.28 (D1)
D2: P1.24 (D2), U1.29 (D2)
D3: P1.25 (D3), U1.30 (D3)
D4: P1.26 (D4), U1.31 (D4)
D5: P1.27 (D5), U1.32 (D5)
D6: P1.28 (D6), U1.33 (D6)
D7: P1.29 (D7), U1.34 (D7)
DCK: P3.36, U1.94 (DCK)
DC_JACK: F2.1, JP1.3
ELP2: FB1.1, P2.OUT
ELP3: FB1.2 (1), P2.IN
ELP4: FB1.3 (1), P2.SD
ELP5: FB1.4 (1), P2.CLK
EM10_EM8: EM8.1, EM10.3
EM10_GND: DC.1 (GND), EM10.2
EM10_POS: DC.2 (DC), EM10.1
GND: -.P$1, AUDIO.2, C1.2, C2.2, C4.2, C5.2, C6.2, C7.2, C9.2, C10.2, C16.2, C17.2, C24.2, C28.1, C29.2, C33.2, C39.2, C40.2, C41.2, C43.2, C45.2, C47.2, C48.2, C49.2, C51.2, EM8.2, EM9.2, GND.TP, GND_BACK.TP, JP1.1, JP2.1, P1.32 (GND), P2.SHIELD (GND), P2.SHIELD1 (GND), P3.33, P3.34, Q1.3 (G), R1.2, SW1.P$7 (GND), SW1.P$8 (GND), U1.19 (GND), U1.44 (GND), U1.49 (TEST0), U1.50 (TEST1), U1.51 (TEST2), U1.54 (PSMD0), U1.55 (PSMD1), U1.58 (!MCS0), U1.59 (!MCS1), U1.84 (GND), U1.108 (GND), U2.21 (GND), U3.2 (SHTDWN), U3.4 (GND), U4.2 (GND), U6.3 (GND), V-.TP, VR1.P$1 (GND), VR1.P$6 (GND), VR1.P$7 (GND)
HP_SWITCH: AUDIO.1, C51.1, R36.1, U3.3 (HP_IN)
LDB0: P3.26, U1.86 (LDB0)
LDB1: P3.27, U1.87 (LDB1)
LDB2: P3.28, U1.88 (LDB2)
LDB3: P3.29, U1.89 (LDB3)
LDB4: P3.30, U1.90 (LDB4)
LDB5: P3.31, U1.91 (LDB5)
LDG0: P3.20, U1.78 (LDG0)
LDG1: P3.21, U1.79 (LDG1)
LDG2: P3.22, U1.80 (LDG2)
LDG3: P3.23, U1.81 (LDG3)
LDG4: P3.24, U1.82 (LDG4)
LDG5: P3.25, U1.83 (LDG5)
LDR0: P3.14, U1.72 (LDR0)
LDR1: P3.15, U1.73 (LDR1)
LDR2: P3.16, U1.74 (LDR2)
LDR3: P3.17, U1.75 (LDR3)
LDR4: P3.18, U1.76 (LDR4)
LDR5: P3.19, U1.77 (LDR5)
LIN_AMP: PIN1.TP, R30.1, R31.2, U3.1 (LIN)
LP: P3.35, U1.93 (LP)
M1: U1.56 (M1)
MA0: U1.99 (MA0), U2.17 (A0)
MA1: U1.98 (MA1), U2.16 (A1)
MA2: U1.97 (MA2), U2.15 (A2)
MA3: U1.124 (MA3), U2.14 (A3)
MA4: U1.123 (MA4), U2.13 (A4)
MA5: U1.122 (MA5), U2.12 (A5)
MA6: U1.121 (MA6), U2.11 (A6)
MA7: U1.120 (MA7), U2.10 (A7)
MA8: U1.115 (MA8), U2.4 (A8)
MA9: U1.114 (MA9), U2.3 (A9)
MA10: U1.111 (MA10), U2.28 (A10)
MA11: U1.113 (MA11), U2.2 (A11)
MA12: U1.119 (MA12), U2.9 (A12)
MD0: U1.100 (MD0), U2.18 (DQ0)
MD1: U1.101 (MD1), U2.19 (DQ1)
MD2: U1.102 (MD2), U2.20 (DQ2)
MD3: U1.103 (MD3), U2.22 (DQ3)
MD4: U1.104 (MD4), U2.23 (DQ4)
MD5: U1.105 (MD5), U2.24 (DQ5)
MD6: U1.106 (MD6), U2.25 (DQ6)
MD7: U1.109 (MD7), U2.26 (DQ7)
MD8: U1.67 (MD8)
MD9: U1.66 (MD9)
MD10: U1.65 (MD10)
MD11: U1.64 (MD11)
MD12: U1.63 (MD12)
MD13: U1.62 (MD13)
MD14: U1.61 (MD14)
MD15: U1.60 (MD15)
MOD: U1.68 (MOD)
unnamed: C7.1, FB1.8 (2), RA3A.1
unnamed: C6.1, FB1.7 (2), RA3B.1
unnamed: C52.2, R30.2
unnamed: C53.2, R32.2
unnamed: C5.1, FB1.6 (2), RA3C.1
unnamed: C52.1, VR1.P$3 (LIN)
unnamed: R27.1, U1.6 (!WR)
unnamed: C4.1, FB1.5 (2), RA3D.1
unnamed: C53.1, VR1.P$2 (RIN)
unnamed: R1.1, SW1.P$4 (4)
unnamed: D1.C, EM7.1
unnamed: EM7.2, F2.2
unnamed: EM6.2, PTC1.2
unnamed: EM9.1, P2.GND
unnamed: C49.1, U3.7 (BYPASS)
P00: P3.41, U1.1 (P00)
P01: P3.42, U1.4 (P01)
P02: P3.43, U1.3 (P02)
P03: P3.44, U1.2 (P03)
P10: P3.45, P10.TP, U1.125 (P10)
P11: P3.46, P11.TP, U1.126 (P11)
P12: P3.47, U1.128 (P12)
P13: P3.48, U1.127 (P13)
PFET_DRAIN: PTC1.1, Q1.1 (D1), Q1.2 (D2), Q1.5 (D5), Q1.6 (D6)
PS: U1.92 (PS)
PUSH: P3.4, PSH_IN.TP, PUSH.TP
R0: U1.45 (R0)
R1: U1.46 (R1)
R2: U1.47 (R2)
R3: U1.48 (R3)
R4: RA3C.2, U1.96 (R4)
RA0: U1.116 (RA0), U2.5 (A13)
RA1: U1.118 (RA1), U2.8 (A14)
RA1-S01: C19.2, RA1A.2
RA1-S02: C18.2, RA1B.2
RD: P1.4 (!RD), U1.7 (!RD)
RES: C17.1, C47.1, P1.30 (!RST), R3.2, RST.TP, U1.35 (!RESET), U6.1 (!RESET)
RIN_AMP: PIN5.TP, R32.1, R33.2, U3.5 (RIN)
ROCK_DOWN: P3.10, ROCKDOWN.TP
ROUT: AUDIO.3, R33.1, ROUT.TP, ROUT1.TP, U3.6 (ROUT)
RPP: D1.A, EM10.4
S01: C19.1, S01.TP, U1.37 (S01)
S02: C18.1, S02.TP, U1.38 (S02)
SCK: R26.1, RA3D.2, U1.40 (SCK)
SIN: RA3B.2, U1.41 (SIN)
SOUT: RA3A.2, U1.42 (SOUT)
SPK+: P3.49, SPK+.TP, U3.8 (BTL+)
SPK-: AUDIO.4, LOUT.TP, P3.50, R31.1, SPK-.TP, U3.10 (LOUT/BTL-)
SPL: P3.13, U1.71 (SPL)
SPS: P3.6, U1.69 (SPS)
SW1B: DC.4 (SWB), F1.2
VCC: JP1.4, Q1.4 (S), SW1.P$2 (2), VCC.TP, VCC_BACK.TP
VCC_SW: JP1.5, P3.1, P3.2, SW1.P$1 (1)
VIN: P1.31 (SND), U1.36 (VIN)
VR1-S01: JP2.2, RA1A.1, VR1.P$5 (VR1-S01)
VR1-S02: JP2.3, RA1B.1, VR1.P$4 (VR1-S02)
WR: P1.3 (!WR), R27.2

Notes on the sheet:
5 3 1
6 4 2
BUTTONS HAVE INTERNAL PULL-UP TO 3.3V
SELECT START B A
RIGHT DOWN UP LEFT
TPS3840DL35
R30 & R32 value: 100k = OEM volume
LOUT
DMGC-IPS has a 100uF DC blocking capacitor in series w/ speaker
DMGC-HDP has a 100uF DC blocking capacitors in series with ROUT/LOUT
PRO-SOUND

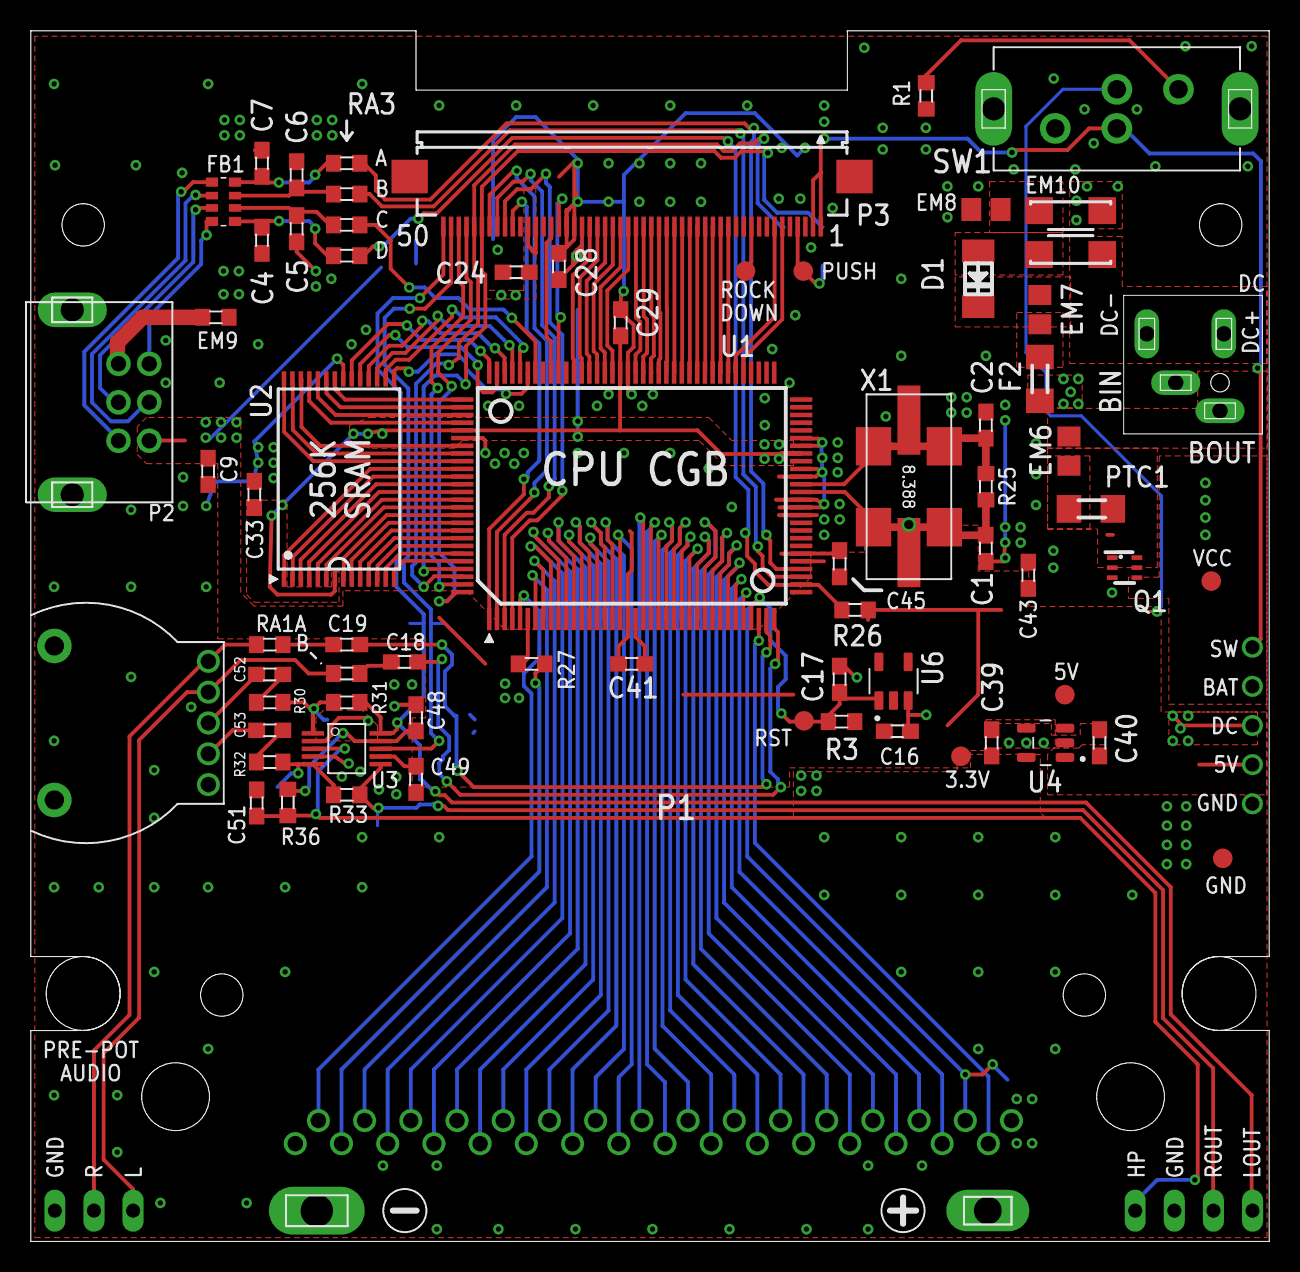
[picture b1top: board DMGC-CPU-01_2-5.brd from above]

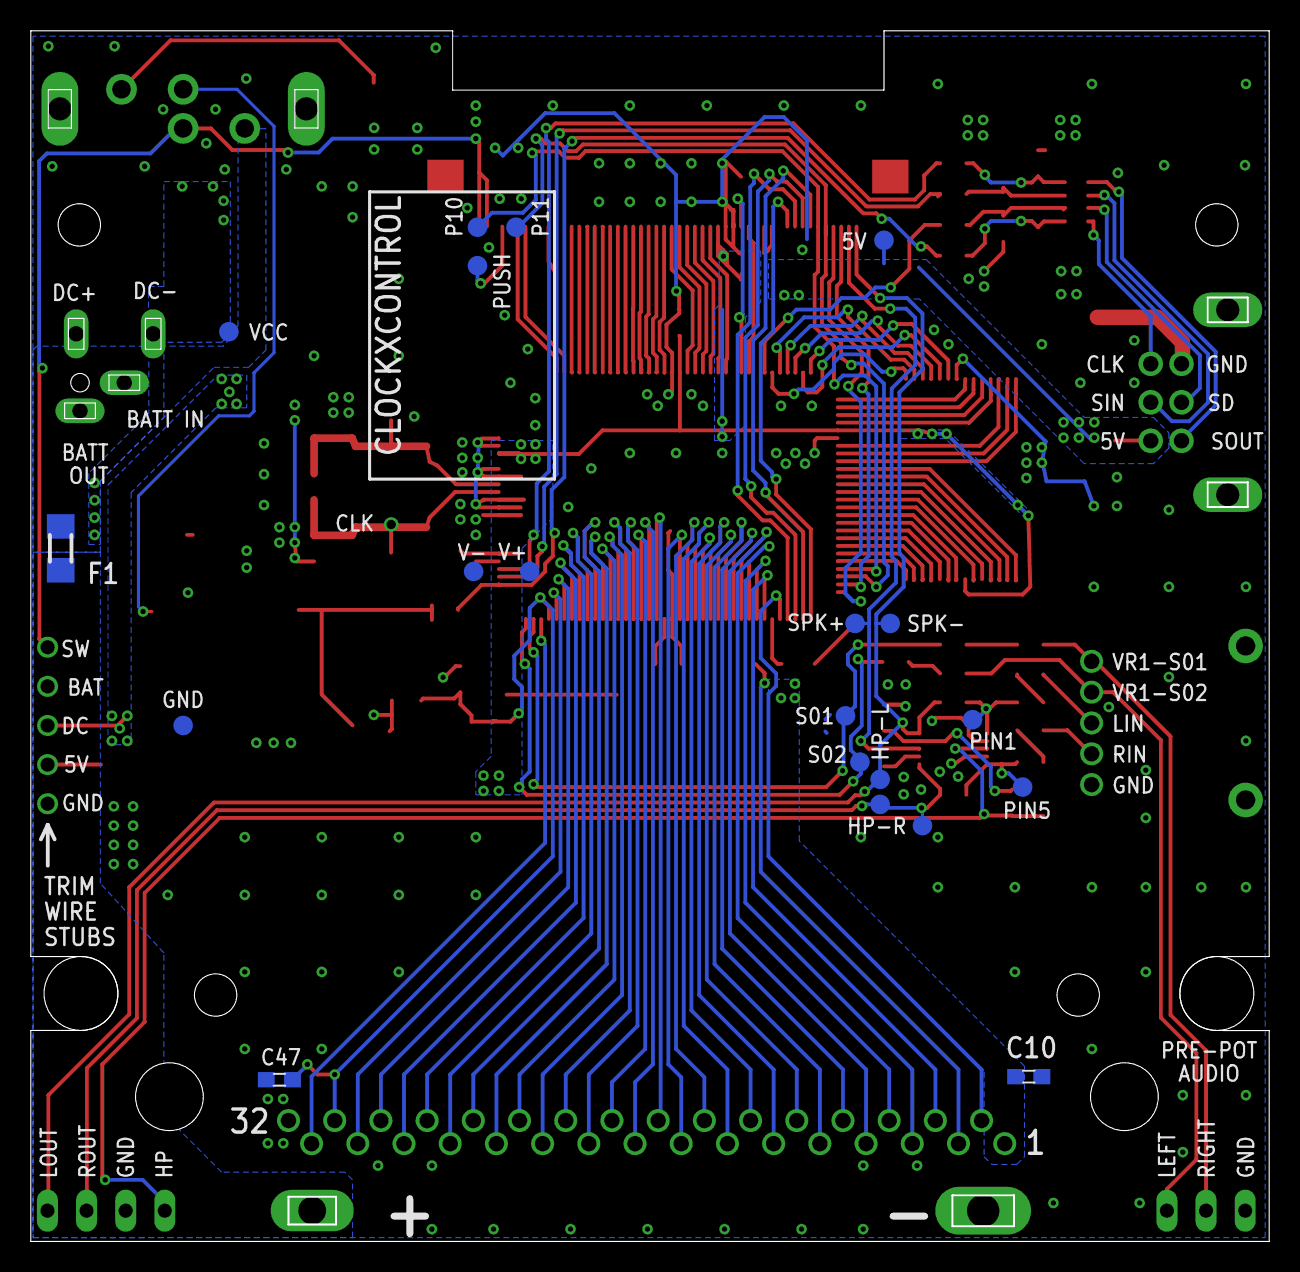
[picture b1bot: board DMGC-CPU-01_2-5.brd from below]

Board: 2 copper layers, 80.4 x 78.6 mm, 95 parts (20 on the bottom side), 140 nets.
